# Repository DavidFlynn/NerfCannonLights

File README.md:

# NerfCannonLights
PIC16F1847, 24 Bit Output PCB

NerfCannonLights receives a pulse from the gun controller and flashes the lights down the barrel.
Open Source GPL v2

Based on a PIC16F1847 and using 3 74HC259 addressable latches to drive transistor outputs.

7 to 24VDC input
I2C is optional, but not used in this version.
200mA per output, 2 amp total for the PCB.

David Flynn
dflynn@oxfordvue.com
(w) +1-626-256-6557
(m) +1-626-893-6654
Oxford V.U.E., Inc.
11711 Clark Street #108
Arcadia, CA 91006 USA

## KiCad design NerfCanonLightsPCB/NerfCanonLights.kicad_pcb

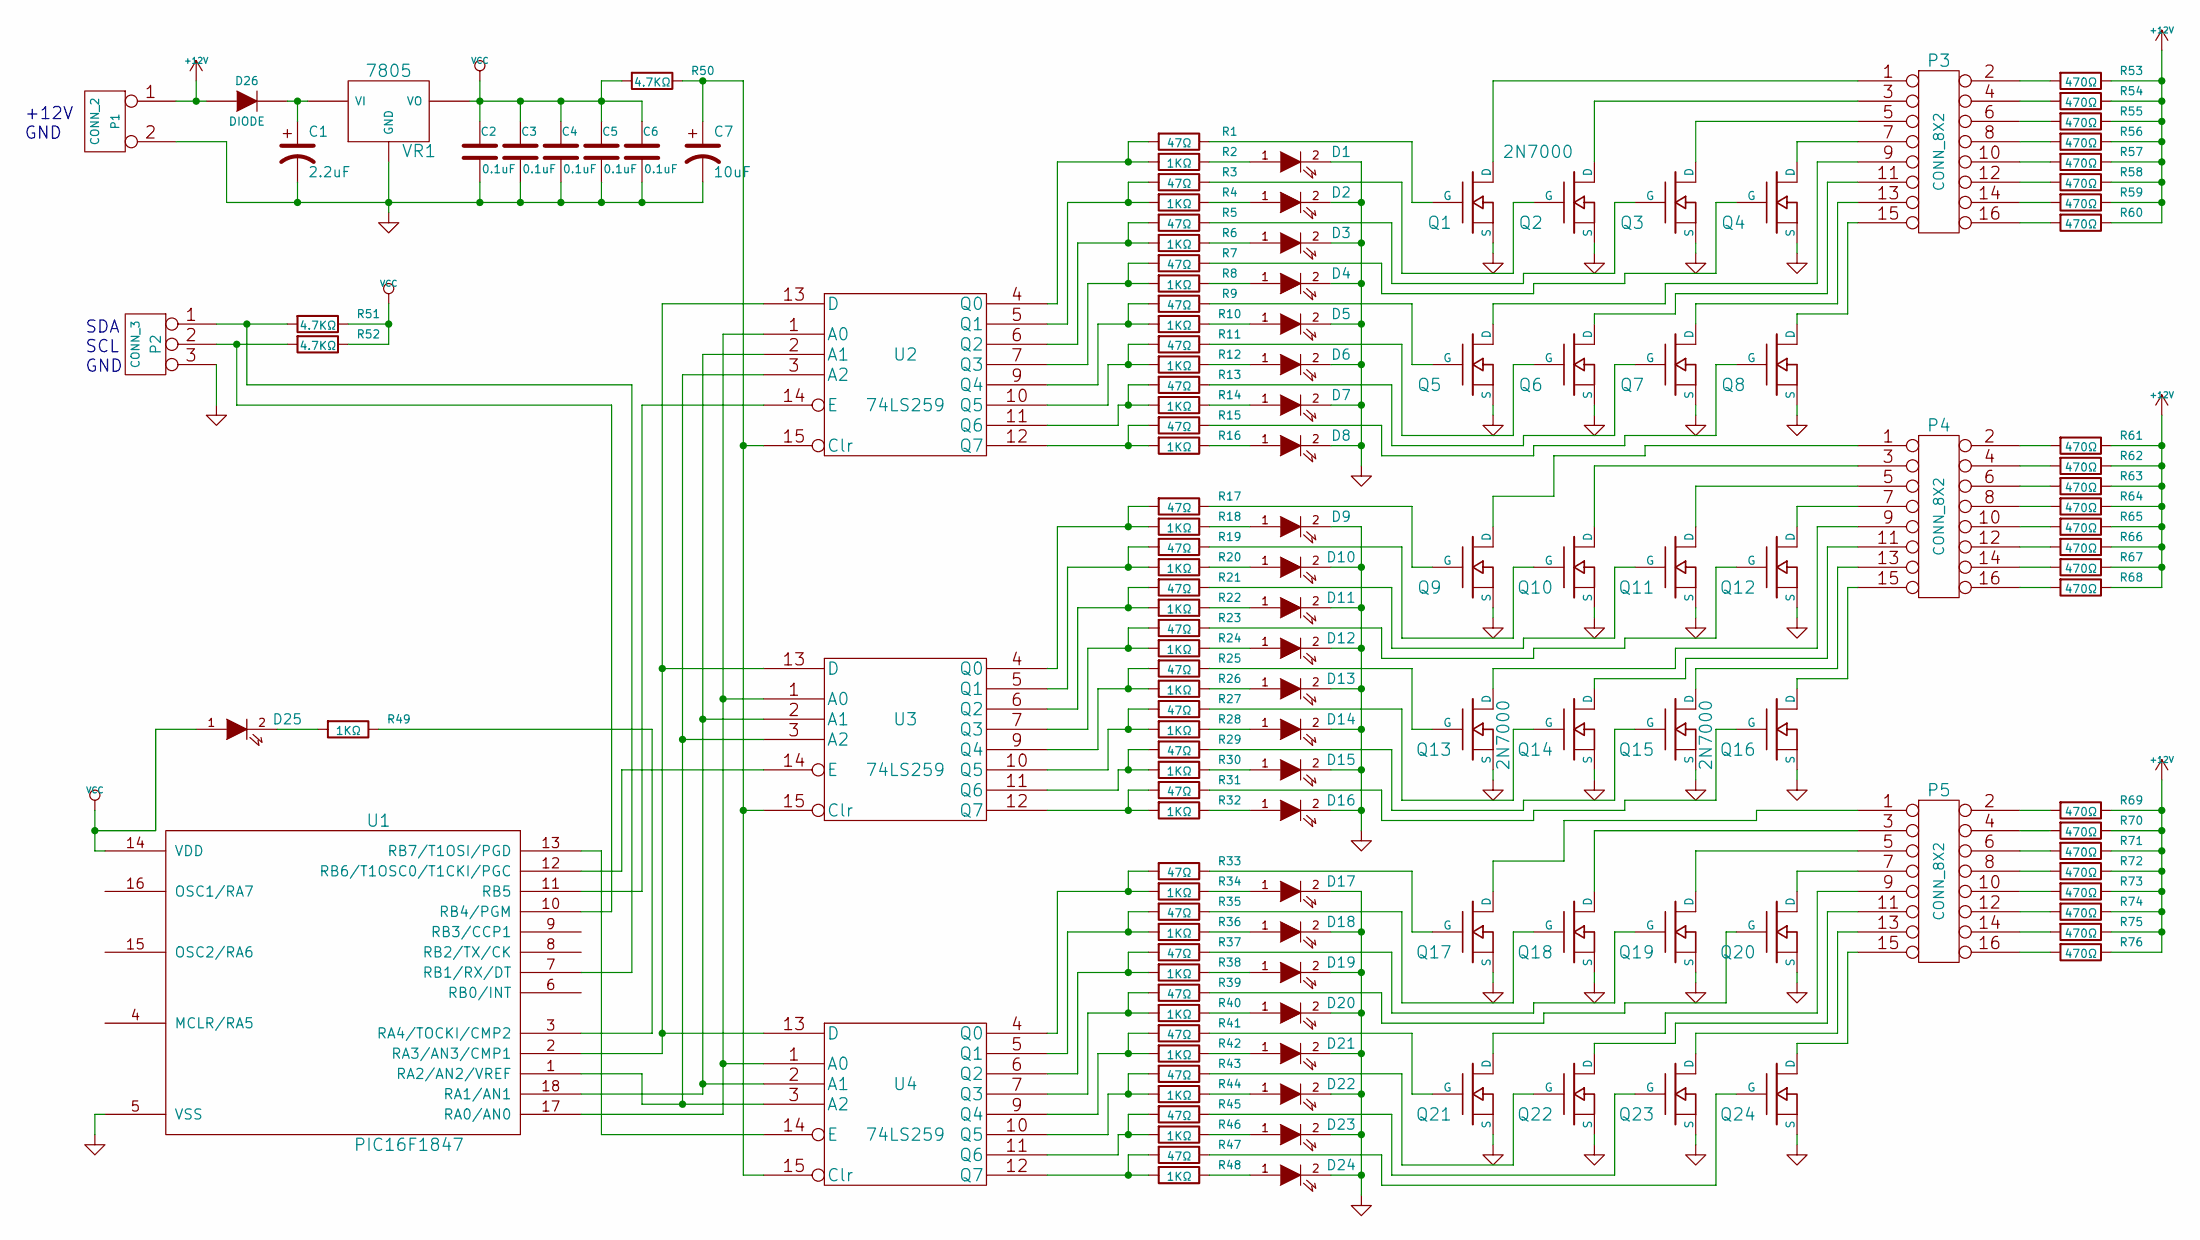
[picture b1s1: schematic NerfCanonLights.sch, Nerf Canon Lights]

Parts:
C1: 2.2uF; C_Radial_D5_L6_P2.5
C2, C3, C4, C5, C6: 0.1uF; C_0805_HandSoldering
C7: 10uF; Elko_vert_11.5x8mm_RM3.5
D1, D2, D3, D4, D5, D6, D7, D8, D9, D10, D11, D12, D13, D14, D15, D16, D17, D18, D19, D20, D21, D22, D23, D24, D25: LED; LED-1206
D26: DIODE; Diode-SMA_Handsoldering
P1: CONN_2; bornier2
P2: CONN_3; bornier3
P3, P4, P5: CONN_8X2; Pin_Header_Straight_2x08
Q1, Q2, Q3, Q4, Q5, Q6, Q7, Q8, Q9, Q10, Q11, Q12, Q13, Q14, Q15, Q16, Q17, Q18, Q19, Q20, Q21, Q22, Q23, Q24: 2N7000; TO92DGS
R1, R3, R5, R7, R9, R11, R13, R15, R17, R19, R21, R23, R25, R27, R29, R31, R33, R35, R37, R39, R41, R43, R45, R47: 47Ω; R_0805_HandSoldering
R2, R4, R6, R8, R10, R12, R14, R16, R18, R20, R22, R24, R26, R28, R30, R32, R34, R36, R38, R40, R42, R44, R46, R48, R49: 1KΩ; R_0805_HandSoldering
R50, R51, R52: 4.7KΩ; R_0805_HandSoldering
R53, R54, R55, R56, R57, R58, R59, R60, R61, R62, R63, R64, R65, R66, R67, R68, R69, R70, R71, R72, R73, R74, R75, R76: 470Ω; R_0805_HandSoldering
U1: PIC16F1847; DIP-18__300
U2, U3, U4: 74LS259; SOIC-16_3.9x9.9mm_Pitch1.27mm
VR1: 7805; LM78XXV

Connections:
+12V: D26.1 (A), P1.1, R53.1, R54.1, R55.1, R56.1, R57.1, R58.1, R59.1, R60.1, R61.1, R62.1, R63.1, R64.1, R65.1, R66.1, R67.1, R68.1, R69.1, R70.1, R71.1, R72.1, R73.1, R74.1, R75.1, R76.1
GND: C1.2, C2.2, C3.2, C4.2, C5.2, C6.2, C7.2, D1.2 (K), D2.2 (K), D3.2 (K), D4.2 (K), D5.2 (K), D6.2 (K), D7.2 (K), D8.2 (K), D9.2 (K), D10.2 (K), D11.2 (K), D12.2 (K), D13.2 (K), D14.2 (K), D15.2 (K), D16.2 (K), D17.2 (K), D18.2 (K), D19.2 (K), D20.2 (K), D21.2 (K), D22.2 (K), D23.2 (K), D24.2 (K), P1.2 (PM), P2.3, Q1.S, Q2.S, Q3.S, Q4.S, Q5.S, Q6.S, Q7.S, Q8.S, Q9.S, Q10.S, Q11.S, Q12.S, Q13.S, Q14.S, Q15.S, Q16.S, Q17.S, Q18.S, Q19.S, Q20.S, Q21.S, Q22.S, Q23.S, Q24.S, U1.5 (VSS), U2.8 (GND), U3.8 (GND), U4.8 (GND), VR1.GND
unnamed: C1.1, D26.2 (K), VR1.VI
unnamed: C7.1, R50.1, U2.15 (Clr), U3.15 (Clr), U4.15 (Clr)
unnamed: D1.1 (A), R2.1
unnamed: D2.1 (A), R4.1
unnamed: D3.1 (A), R6.1
unnamed: D4.1 (A), R8.1
unnamed: D5.1 (A), R10.1
unnamed: D6.1 (A), R12.1
unnamed: D7.1 (A), R14.1
unnamed: D8.1 (A), R16.1
unnamed: D9.1 (A), R18.1
unnamed: D10.1 (A), R20.1
unnamed: D11.1 (A), R22.1
unnamed: D12.1 (A), R24.1
unnamed: D13.1 (A), R26.1
unnamed: D14.1 (A), R28.1
unnamed: D15.1 (A), R30.1
unnamed: D16.1 (A), R32.1
unnamed: D17.1 (A), R34.1
unnamed: D18.1 (A), R36.1
unnamed: D19.1 (A), R38.1
unnamed: D20.1 (A), R40.1
unnamed: D21.1 (A), R42.1
unnamed: D22.1 (A), R44.1
unnamed: D23.1 (A), R46.1
unnamed: D24.1 (A), R48.1
unnamed: D25.2 (K), R49.2
unnamed: P2.1, R51.2, U1.7 (RB1/RX/DT)
unnamed: P2.2 (PM), R52.2, U1.10 (RB4/PGM)
unnamed: P3.1, Q1.D
unnamed: P3.2, R53.2
unnamed: P3.3, Q2.D
unnamed: P3.4, R54.2
unnamed: P3.5, Q3.D
unnamed: P3.6, R55.2
unnamed: P3.7, Q4.D
unnamed: P3.8, R56.2
unnamed: P3.9, Q5.D
unnamed: P3.10, R57.2
unnamed: P3.11, Q6.D
unnamed: P3.12, R58.2
unnamed: P3.13, Q7.D
unnamed: P3.14, R59.2
unnamed: P3.15, Q8.D
unnamed: P3.16, R60.2
unnamed: P4.1, Q9.D
unnamed: P4.2, R61.2
unnamed: P4.3, Q10.D
unnamed: P4.4, R62.2
unnamed: P4.5, Q11.D
unnamed: P4.6, R63.2
unnamed: P4.7, Q12.D
unnamed: P4.8, R64.2
unnamed: P4.9, Q13.D
unnamed: P4.10, R65.2
unnamed: P4.11, Q14.D
unnamed: P4.12, R66.2
unnamed: P4.13, Q15.D
unnamed: P4.14, R67.2
unnamed: P4.15, Q16.D
unnamed: P4.16, R68.2
unnamed: P5.1, Q17.D
unnamed: P5.2, R69.2
unnamed: P5.3, Q18.D
unnamed: P5.4, R70.2
unnamed: P5.5, Q19.D
unnamed: P5.6, R71.2
unnamed: P5.7, Q20.D
unnamed: P5.8, R72.2
unnamed: P5.9, Q21.D
unnamed: P5.10, R73.2
unnamed: P5.11, Q22.D
unnamed: P5.12, R74.2
unnamed: P5.13, Q23.D
unnamed: P5.14, R75.2
unnamed: P5.15, Q24.D
unnamed: P5.16, R76.2
unnamed: Q1.G, R1.1
unnamed: Q2.G, R3.1
unnamed: Q3.G, R5.1
unnamed: Q4.G, R7.1
unnamed: Q5.G, R9.1
unnamed: Q6.G, R11.1
unnamed: Q7.G, R13.1
unnamed: Q8.G, R15.1
unnamed: Q9.G, R17.1
unnamed: Q10.G, R19.1
unnamed: Q11.G, R21.1
unnamed: Q12.G, R23.1
unnamed: Q13.G, R25.1
unnamed: Q14.G, R27.1
unnamed: Q15.G, R29.1
unnamed: Q16.G, R31.1
unnamed: Q17.G, R33.1
unnamed: Q18.G, R35.1
unnamed: Q19.G, R37.1
unnamed: Q20.G, R39.1
unnamed: Q21.G, R41.1
unnamed: Q22.G, R43.1
unnamed: Q23.G, R45.1
unnamed: Q24.G, R47.1
unnamed: R1.2, R2.2, U2.4 (Q0)
unnamed: R3.2, R4.2, U2.5 (Q1)
unnamed: R5.2, R6.2, U2.6 (Q2)
unnamed: R7.2, R8.2, U2.7 (Q3)
unnamed: R9.2, R10.2, U2.9 (Q4)
unnamed: R11.2, R12.2, U2.10 (Q5)
unnamed: R13.2, R14.2, U2.11 (Q6)
unnamed: R15.2, R16.2, U2.12 (Q7)
unnamed: R17.2, R18.2, U3.4 (Q0)
unnamed: R19.2, R20.2, U3.5 (Q1)
unnamed: R21.2, R22.2, U3.6 (Q2)
unnamed: R23.2, R24.2, U3.7 (Q3)
unnamed: R25.2, R26.2, U3.9 (Q4)
unnamed: R27.2, R28.2, U3.10 (Q5)
unnamed: R29.2, R30.2, U3.11 (Q6)
unnamed: R31.2, R32.2, U3.12 (Q7)
unnamed: R33.2, R34.2, U4.4 (Q0)
unnamed: R35.2, R36.2, U4.5 (Q1)
unnamed: R37.2, R38.2, U4.6 (Q2)
unnamed: R39.2, R40.2, U4.7 (Q3)
unnamed: R41.2, R42.2, U4.9 (Q4)
unnamed: R43.2, R44.2, U4.10 (Q5)
unnamed: R45.2, R46.2, U4.11 (Q6)
unnamed: R47.2, R48.2, U4.12 (Q7)
unnamed: R49.1, U1.3 (RA4/TOCKI/CMP2)
unnamed: U1.1 (RA2/AN2/VREF), U2.3 (A2), U3.3 (A2), U4.3 (A2)
unnamed: U1.2 (RA3/AN3/CMP1), U2.13 (D), U3.13 (D), U4.13 (D)
unnamed: U1.11 (RB5), U2.14 (E)
unnamed: U1.12 (RB6/T1OSC0/T1CKI/PGC), U3.14 (E)
unnamed: U1.13 (RB7/T1OSI/PGD), U4.14 (E)
unnamed: U1.17 (RA0/AN0), U2.1 (A0), U3.1 (A0), U4.1 (A0)
unnamed: U1.18 (RA1/AN1), U2.2 (A1), U3.2 (A1), U4.2 (A1)
VCC: C2.1, C3.1, C4.1, C5.1, C6.1, D25.1 (A), R50.2, R51.1, R52.1, U1.14 (VDD), U2.16 (VCC), U3.16 (VCC), U4.16 (VCC), VR1.VO

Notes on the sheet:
SDA SCL GND
+12V GND

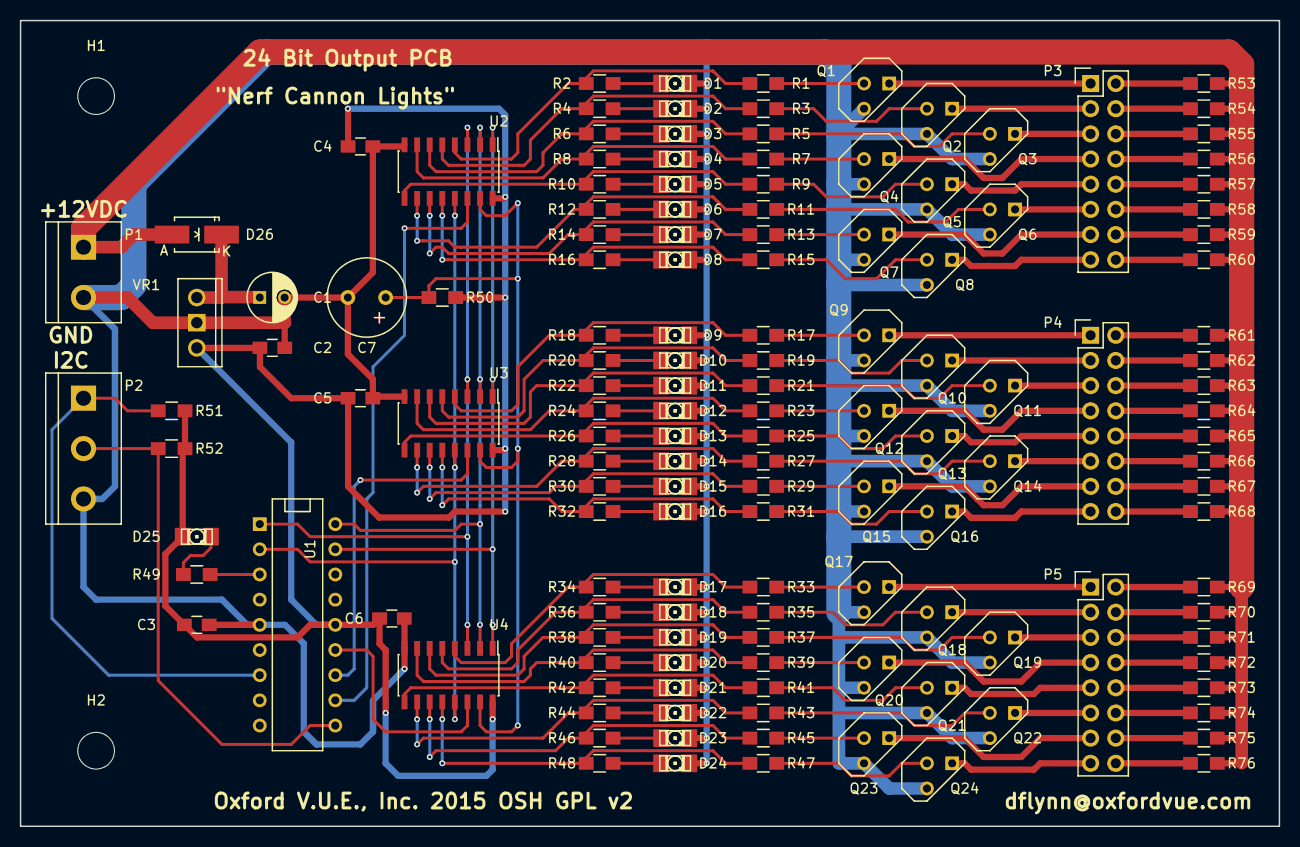
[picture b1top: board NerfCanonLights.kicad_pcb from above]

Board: 2 copper layers, 127.0 x 81.3 mm, 145 parts (0 on the bottom side), 136 nets.

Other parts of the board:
H1, H2: MountingHole_3-7mm

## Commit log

2015-04-22 Notes first

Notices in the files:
NerfCanonLightsPCB/NerfCanonLights.kicad_pcb:
OSH, GPL V2
Oxford V.U.E., Inc. 2015 OSH GPL v2
NerfCanonLightsPCB/NerfCanonLights.sch:
GPL 2 Open Source
